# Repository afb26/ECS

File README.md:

# Battle Bots Equal Control System

**The Equal Control System (ECS) is a project for use in Battle Bots competitions that allows each competitor a plug and play solution to control.**
Please see code/README.md for instructions on using.

**Features**
- Control Battle Bots using a web interface.
- Drive up to 6 servos (or more) and communicate with up to 4 (or more) motor drivers.
- See pcb/PCB.md for more details.

**In this repository**
- Code for the ECS unit
- the PCB schematic
- the 3D Prints files for the case
- documents about use

**Parts for the prints**
- 4 x 10mm [Countersunk Screws](https://www.boltandnut.com.au/m3-x-0-50p-metric-coarse-plain-black-grade-12-9-countersunk-head-socket-2mm-key-screws)
- 4 x M3 [Threaded Insert](https://www.amazon.com.au/dp/B0B4248K76?psc=1&ref=ppx_yo2ov_dt_b_product_details)

**Compatible Motor Driver Chips**
- [TB6612](https://www.adafruit.com/product/2448)
- [L298N](https://www.auselectronicsdirect.com.au/l298n-dual-h-bridge-motor-controller-module-for-ar)  
If the motor driver you wish to use is not included, please raise an issue on GitHub with a link to the motor driver. Refer to ISSUES.md for instructions.

**To Do**
- PCB Files + Ordering Instructions
- Case Assembly Instructions
- Comment code explaining function
- Add competition code

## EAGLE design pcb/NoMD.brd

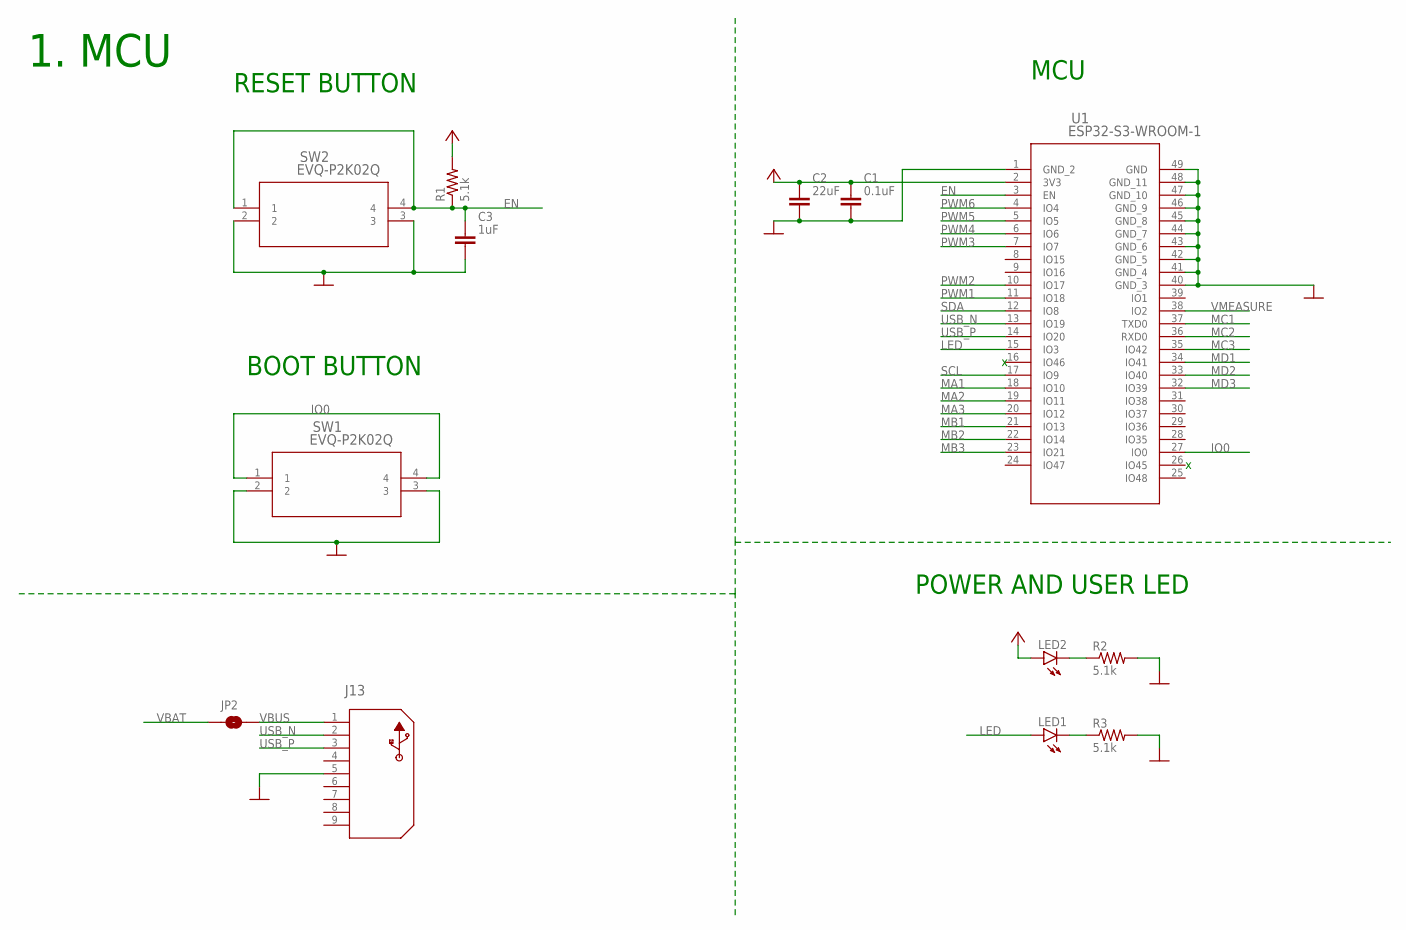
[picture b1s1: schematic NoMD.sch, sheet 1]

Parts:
C1: 0.1uF; CAPC1005X60
C2: 22uF; CAPC1005X60
C3: 1uF; CAPC1005X60
J13: 1734035-2; CONN5_USB1734035_TEC
JP2: JUMPER-SMT_2_NO_SILK; SMT-JUMPER_2_NO_SILK
LED1, LED2: LEDCHIPLED_0603; CHIPLED_0603
R1, R2, R3: 5.1k; R0402
SW1, SW2: EVQ-P2K02Q; EVQP2K_PAN
U1: ESP32-S3-WROOM-1; ESP32-S3-WROOM-1_EXP

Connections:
+3V3: C1.1, C2.1, LED2.A, R1.2, U1.2 (3V3); also elsewhere on the board
EN: C3.1, R1.1, SW2.1, SW2.4, U1.3 (EN)
GND: C1.2, C2.2, C3.2, J13.5, R2.2, R3.2, SW1.2, SW1.3, SW2.2, SW2.3, U1.1 (GND_2), U1.40 (GND_3), U1.41 (GND_4), U1.42 (GND_5), U1.43 (GND_6), U1.44 (GND_7), U1.45 (GND_8), U1.46 (GND_9), U1.47 (GND_10), U1.48 (GND_11), U1.49 (GND); also elsewhere on the board
IO0: SW1.1, SW1.4, U1.27 (IO0)
LED: LED1.A, U1.15 (IO3)
MA1: U1.18 (IO10); also elsewhere on the board
MA2: U1.19 (IO11); also elsewhere on the board
MA3: U1.20 (IO12); also elsewhere on the board
MB1: U1.21 (IO13); also elsewhere on the board
MB2: U1.22 (IO14); also elsewhere on the board
MB3: U1.23 (IO21); also elsewhere on the board
MC1: U1.37 (TXD0); also elsewhere on the board
MC2: U1.36 (RXD0); also elsewhere on the board
MC3: U1.35 (IO42); also elsewhere on the board
MD1: U1.34 (IO41); also elsewhere on the board
MD2: U1.33 (IO40); also elsewhere on the board
MD3: U1.32 (IO39); also elsewhere on the board
unnamed: LED2.C, R2.1
unnamed: LED1.C, R3.1
PWM1: U1.11 (IO18); also elsewhere on the board
PWM2: U1.10 (IO17); also elsewhere on the board
PWM3: U1.7 (IO7); also elsewhere on the board
PWM4: U1.6 (IO6); also elsewhere on the board
PWM5: U1.5 (IO5); also elsewhere on the board
PWM6: U1.4 (IO4); also elsewhere on the board
SCL: U1.17 (IO9); also elsewhere on the board
SDA: U1.12 (IO8); also elsewhere on the board
USB_N: J13.2, U1.13 (IO19)
USB_P: J13.3, U1.14 (IO20)
VBAT: JP2.1; also elsewhere on the board
VBUS: J13.1, JP2.2
VMEASURE: U1.38 (IO2); also elsewhere on the board

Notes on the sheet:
1. MCU
RESET BUTTON
BOOT BUTTON
POWER AND USER LED
MCU

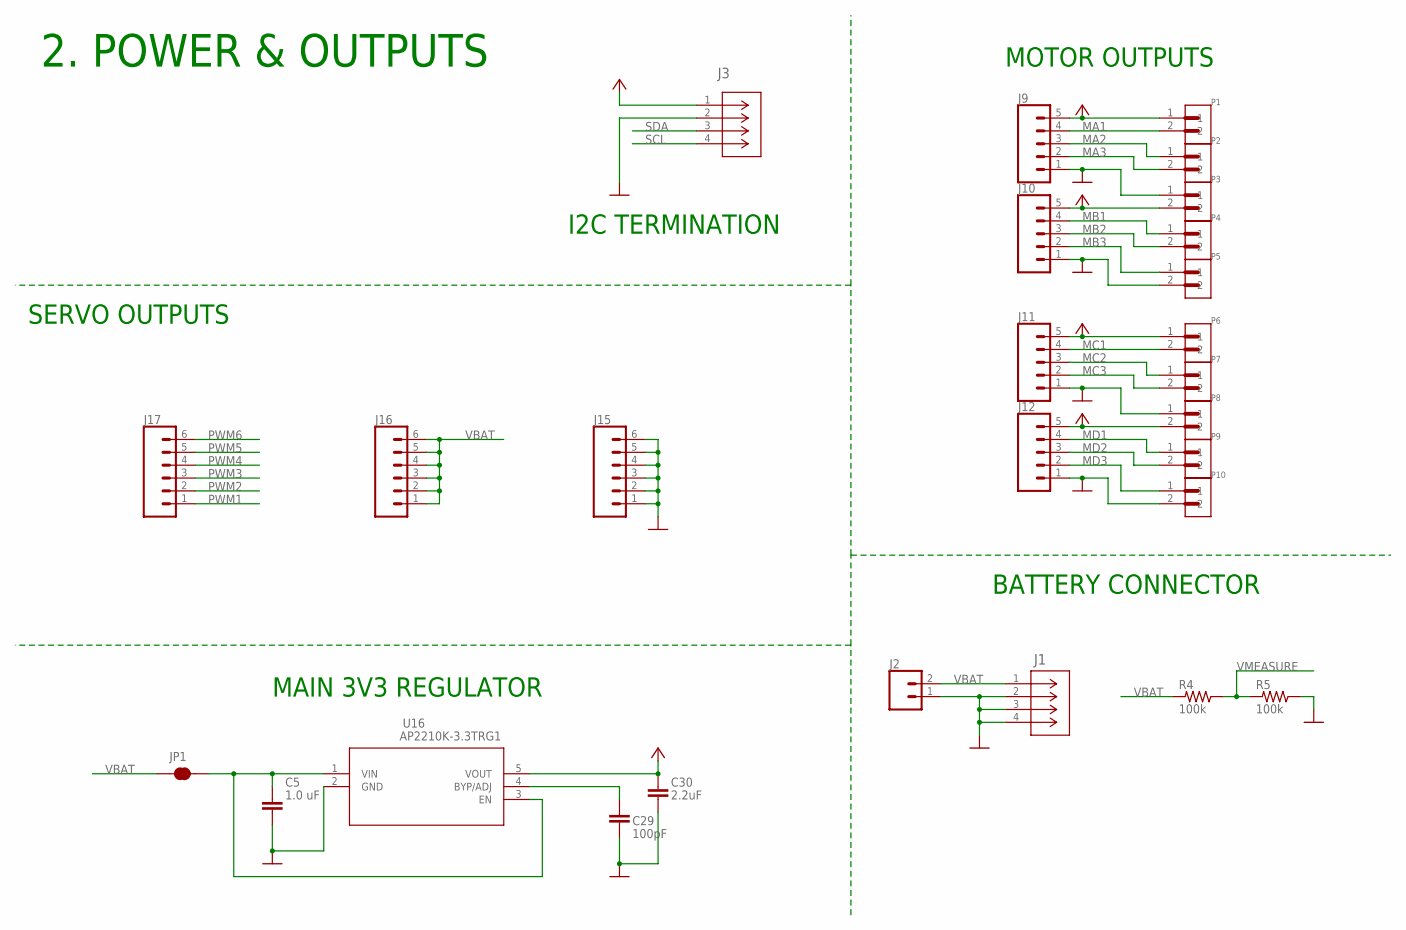
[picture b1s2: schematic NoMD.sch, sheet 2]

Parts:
C5: 1.0 uF; CAPC1005X60
C29: 100pF; CAPC1005X60
C30: 2.2uF; CAPC1005X60
J1: S2B-PH-SM4-TB(LF)(SN); CONN_S2B-PH-SM4-TB_JST
J2: CONN_021X02_NO_SILK; 1X02_NO_SILK
J3: SM04B-SRSS-TB(LF)(SN); CONN_SM04B_JST
J9, J10, J11, J12: CONN_05NO_SILK; 1X05_NO_SILK
J15, J16, J17: CONN_06NO_SILK_NO_POP; 1X06_NO_SILK
JP1: JUMPER-SMT_2_NC_TRACE_NO-SILK; SMT-JUMPER_2_NC_TRACE_NO-SILK
P1, P2, P3, P4, P5, P6, P7, P8, P9, P10: OSTTE020104; OST_OSTTE020104
R4, R5: 100k; R0402
U16: AP2210K-3.3TRG1; SOT-23-5_DIO

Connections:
+3V3: C30.1, J3.1, J9.5, J10.5, J11.5, J12.5, P1.1, P3.2, P6.1, P8.2, U16.5 (VOUT); also elsewhere on the board
GND: C5.2, C29.2, C30.2, J1.2, J1.3 (SHIELD_2), J1.4 (SHIELD), J2.1, J3.2, J9.1, J10.1, J11.1, J12.1, J15.1, J15.2, J15.3, J15.4, J15.5, J15.6, P3.1, P5.2, P8.1, P10.2, R5.1, U16.2 (GND); also elsewhere on the board
MA1: J9.4, P1.2; also elsewhere on the board
MA2: J9.3, P2.1; also elsewhere on the board
MA3: J9.2, P2.2; also elsewhere on the board
MB1: J10.4, P4.1; also elsewhere on the board
MB2: J10.3, P4.2; also elsewhere on the board
MB3: J10.2, P5.1; also elsewhere on the board
MC1: J11.4, P6.2; also elsewhere on the board
MC2: J11.3, P7.1; also elsewhere on the board
MC3: J11.2, P7.2; also elsewhere on the board
MD1: J12.4, P9.1; also elsewhere on the board
MD2: J12.3, P9.2; also elsewhere on the board
MD3: J12.2, P10.1; also elsewhere on the board
unnamed: C29.1, U16.4 (BYP/ADJ)
PWM1: J17.1; also elsewhere on the board
PWM2: J17.2; also elsewhere on the board
PWM3: J17.3; also elsewhere on the board
PWM4: J17.4; also elsewhere on the board
PWM5: J17.5; also elsewhere on the board
PWM6: J17.6; also elsewhere on the board
SCL: J3.4; also elsewhere on the board
SDA: J3.3; also elsewhere on the board
VBAT: C5.1, J1.1, J2.2, J16.1, J16.2, J16.3, J16.4, J16.5, J16.6, JP1.1, JP1.2, R4.2, U16.1 (VIN), U16.3 (EN); also elsewhere on the board
VMEASURE: R4.1, R5.2; also elsewhere on the board

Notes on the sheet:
2. POWER & OUTPUTS
I2C TERMINATION
BATTERY CONNECTOR
MAIN 3V3 REGULATOR
SERVO OUTPUTS
MOTOR OUTPUTS

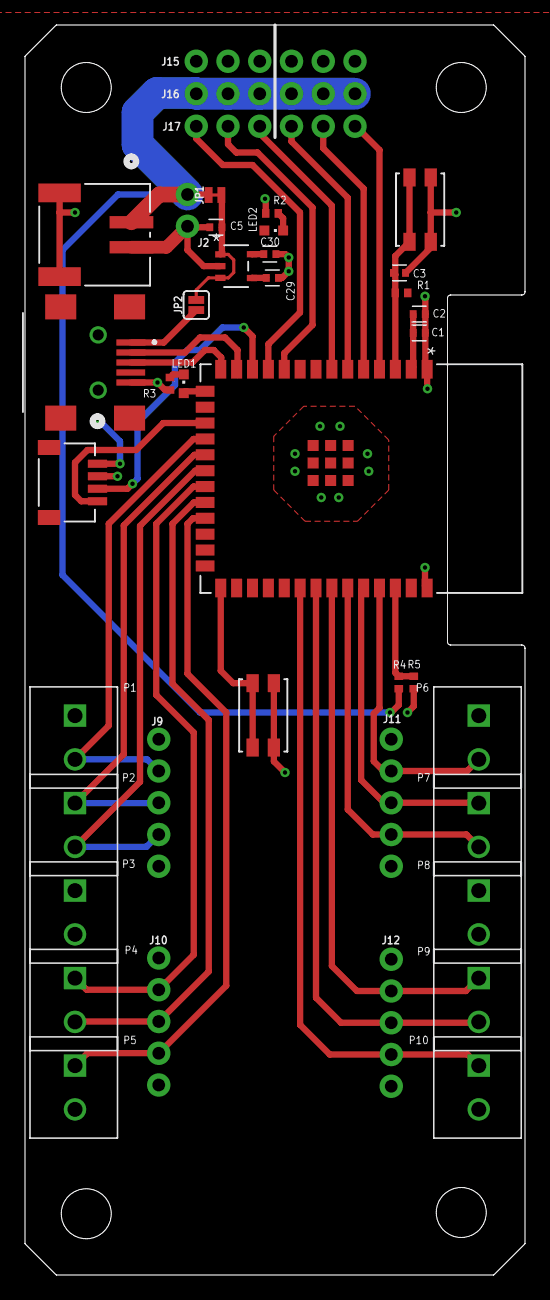
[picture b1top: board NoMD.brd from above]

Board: 2 copper layers, 40.0 x 100.0 mm, 40 parts (0 on the bottom side), 33 nets.

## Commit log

2023-07-18 Inital commit
2023-07-18 Fix README file
2023-09-10 Inital files
2023-10-13 Added images
2023-10-13 Smaller images
2023-10-13 Markdown manual
2023-10-13 Schematic added
2023-10-13 Cleanup
2023-10-13 Full instructions + updated motor driver code
2023-10-18 Refactor motor driver + reorganise files

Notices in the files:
parts and their libraries:
SparkFun-Connectors: Licensing: Creative Commons ShareAlike 4.0 International - https://creativecommons.org/licenses/by-sa/4.0
COPYRIGHT: Copyright (C) 2022 Ultra Librarian. All rights reserved.
COPYRIGHT: Copyright (C) 2023 Ultra Librarian. All rights reserved.
